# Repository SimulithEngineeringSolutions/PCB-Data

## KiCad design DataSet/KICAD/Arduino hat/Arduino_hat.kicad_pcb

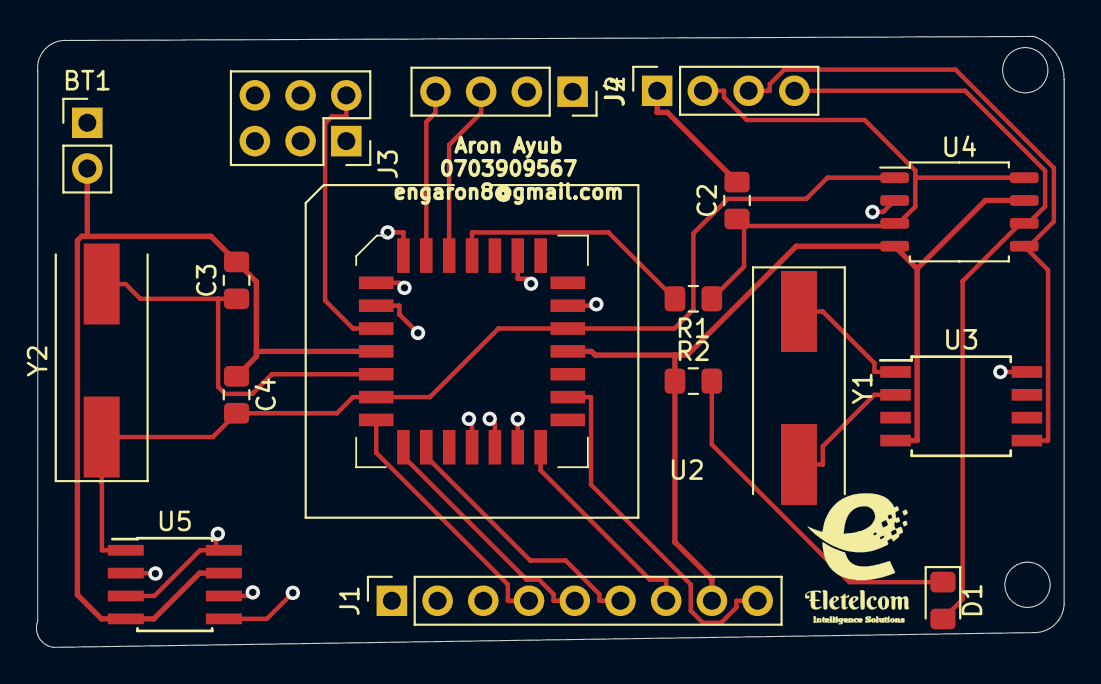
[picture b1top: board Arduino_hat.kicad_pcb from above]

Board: 4 copper layers, 57.1 x 33.9 mm, 17 parts (0 on the bottom side), 22 nets.

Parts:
BT1: 3V; PinHeader_1x02_P2.54mm_Vertical
C2: 10uF; C_0805_2012Metric_Pad1.15x1.40mm_HandSolder
C3, C4: 22pF; C_0805_2012Metric_Pad1.15x1.40mm_HandSolder
D1: LED; LED_0805_2012Metric_Pad1.15x1.40mm_HandSolder
J1: digital pins; PinSocket_1x09_P2.54mm_Vertical
J2: I2C; PinSocket_1x04_P2.54mm_Vertical
J3: ICSP; PinSocket_2x03_P2.54mm_Vertical
J4: serial; PinSocket_1x04_P2.54mm_Vertical
R1: 10Kohm; R_0805_2012Metric_Pad1.15x1.40mm_HandSolder
R2: 330ohm; R_0805_2012Metric_Pad1.15x1.40mm_HandSolder
U2: ATmega328P-PU; PLCC-28_SMD-Socket
U3: DS1337_PDv2; SOIJ-8_5.3x5.3mm_P1.27mm
U4: 24LC1025; SOIC-8_5.275x5.275mm_P1.27mm
U5: 24LC1025; PowerIntegrations_SO-8
Y1: Crystal 32MHz; Crystal_SMD_HC49-SD
Y2: Crystal 16Mhz; Crystal_SMD_HC49-SD

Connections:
/ADDR1: C4.2, U2.10, U2.23, U4.1, U5.1, Y2.1
/ADDR2: U2.24, U4.2, U5.2
/D2: J1.1, U2.4
/D3: J1.2, U2.5
/D4: J1.3, U2.6
/D5: J1.4, U2.11
/D6: J1.5, U2.12
/D7: J1.6, U2.13
/D8: J1.7, U2.18
/MISO: J3.1, U2.16
/MOSI: J3.4, U2.15
/RESET: R1.2, U2.1
/RX: J4.3, U2.2
/SCK: D1.2, J2.4, J3.3, U2.17, U4.6, U5.6
/SDA: J2.3, U2.27, U3.5, U4.5, U5.5
/TX: J4.4, U2.3
/VCC: BT1.1, C2.1, J1.9, J2.2, J3.2, J4.2, R1.1, U2.7, U2.20, U3.8, U4.3, U4.8, U5.3, U5.8
GNDPWR: BT1.2, C2.2, C3.2, C4.1, J1.8, J2.1, J3.6, J4.1, R2.1, U2.8, U2.22, U3.4, U4.4, U4.7, U5.4, U5.7
unnamed: C3.1, U2.9, Y2.2
unnamed: D1.1, R2.2
unnamed: U3.1, Y1.1
unnamed: U3.2, Y1.2

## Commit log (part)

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2026-06-17 file correction
2026-06-17 kicad_pcb push
2026-06-18 ui updates
2026-06-24 integrated circuit addition
2026-06-29 New IC chip maker
